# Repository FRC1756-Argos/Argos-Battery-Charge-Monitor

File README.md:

# Argos-Battery-Charge-Monitor
System to monitor a set of charging batteries

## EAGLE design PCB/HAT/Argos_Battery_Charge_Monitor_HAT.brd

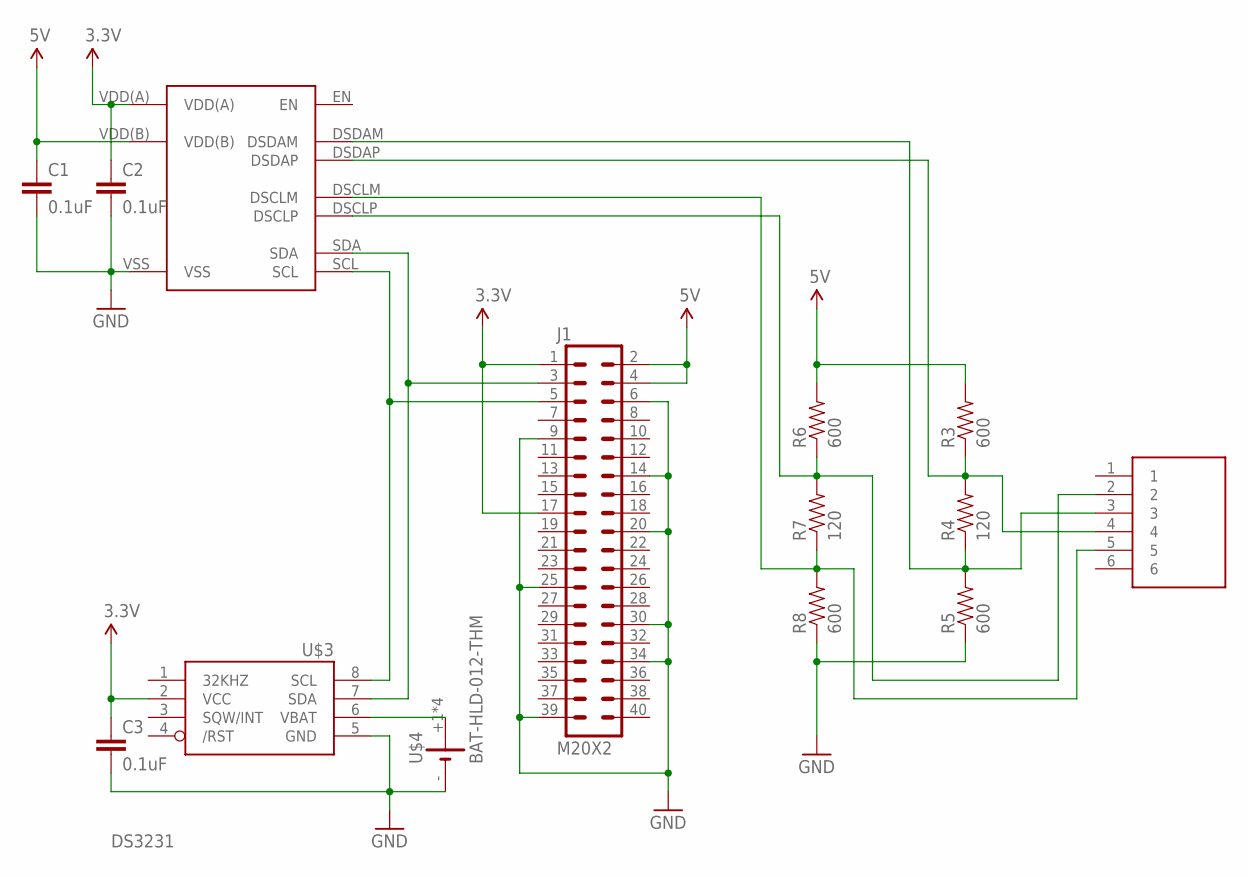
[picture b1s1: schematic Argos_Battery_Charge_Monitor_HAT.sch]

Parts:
C1, C2, C3: 0.1uF; 0805
J1: M20X2; 2X20
R3, R5, R6, R8: 600; 0805
R4, R7: 120; 0805
U$1: E5566-Q0LK22-L
U$2: SOP50P490X110-10N
U$3: DS3231MZ; SOIC8
U$4: BAT-HLD-012-THM

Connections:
3.3V: C2.1, C3.1, J1.1, J1.17, U$2.VDD(A), U$3.2 (VCC)
5V: C1.1, J1.2, J1.4, R3.2, R6.2, U$2.VDD(B)
D_SCL_M: R7.1, R8.2, U$1.5, U$2.DSCLM
D_SCL_P: R6.1, R7.2, U$1.2, U$2.DSCLP
D_SDA_M: R4.1, R5.2, U$1.3, U$2.DSDAM
D_SDA_P: R3.1, R4.2, U$1.4, U$2.DSDAP
GND: C1.2, C2.2, C3.2, J1.6, J1.9, J1.14, J1.20, J1.25, J1.30, J1.34, J1.39, R5.1, R8.1, U$2.VSS, U$3.5 (GND), U$4.-
unnamed: U$3.6 (VBAT), U$4.+1 (+), U$4.+2 (+), U$4.+3 (+), U$4.+4 (+)
SCL: J1.5, U$2.SCL, U$3.8 (SCL)
SDA: J1.3, U$2.SDA, U$3.7 (SDA)

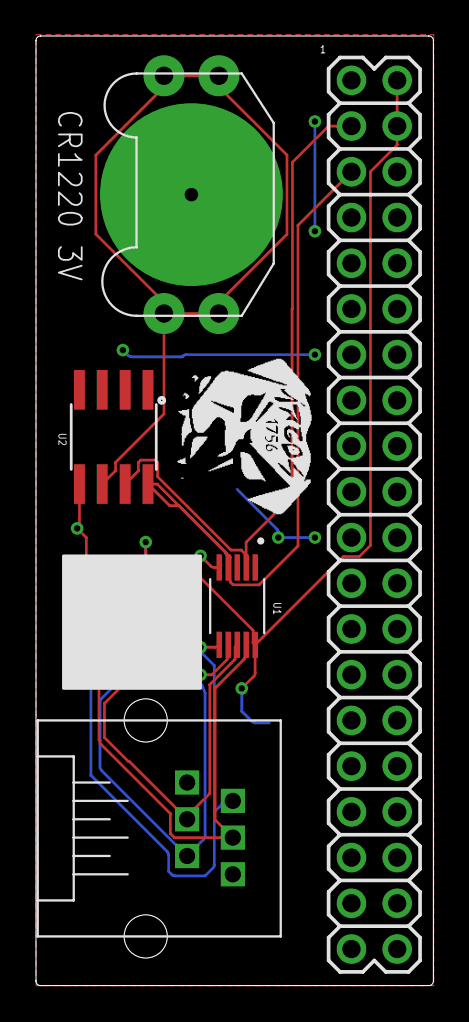
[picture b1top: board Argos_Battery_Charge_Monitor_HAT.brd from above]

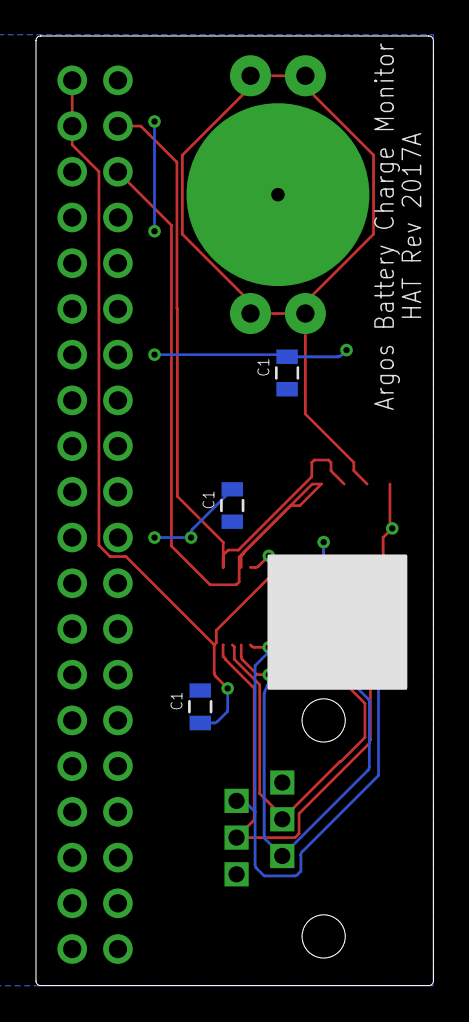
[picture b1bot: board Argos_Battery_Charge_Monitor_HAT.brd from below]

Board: 2 copper layers, 22.1 x 52.8 mm, 14 parts (6 on the bottom side), 10 nets.

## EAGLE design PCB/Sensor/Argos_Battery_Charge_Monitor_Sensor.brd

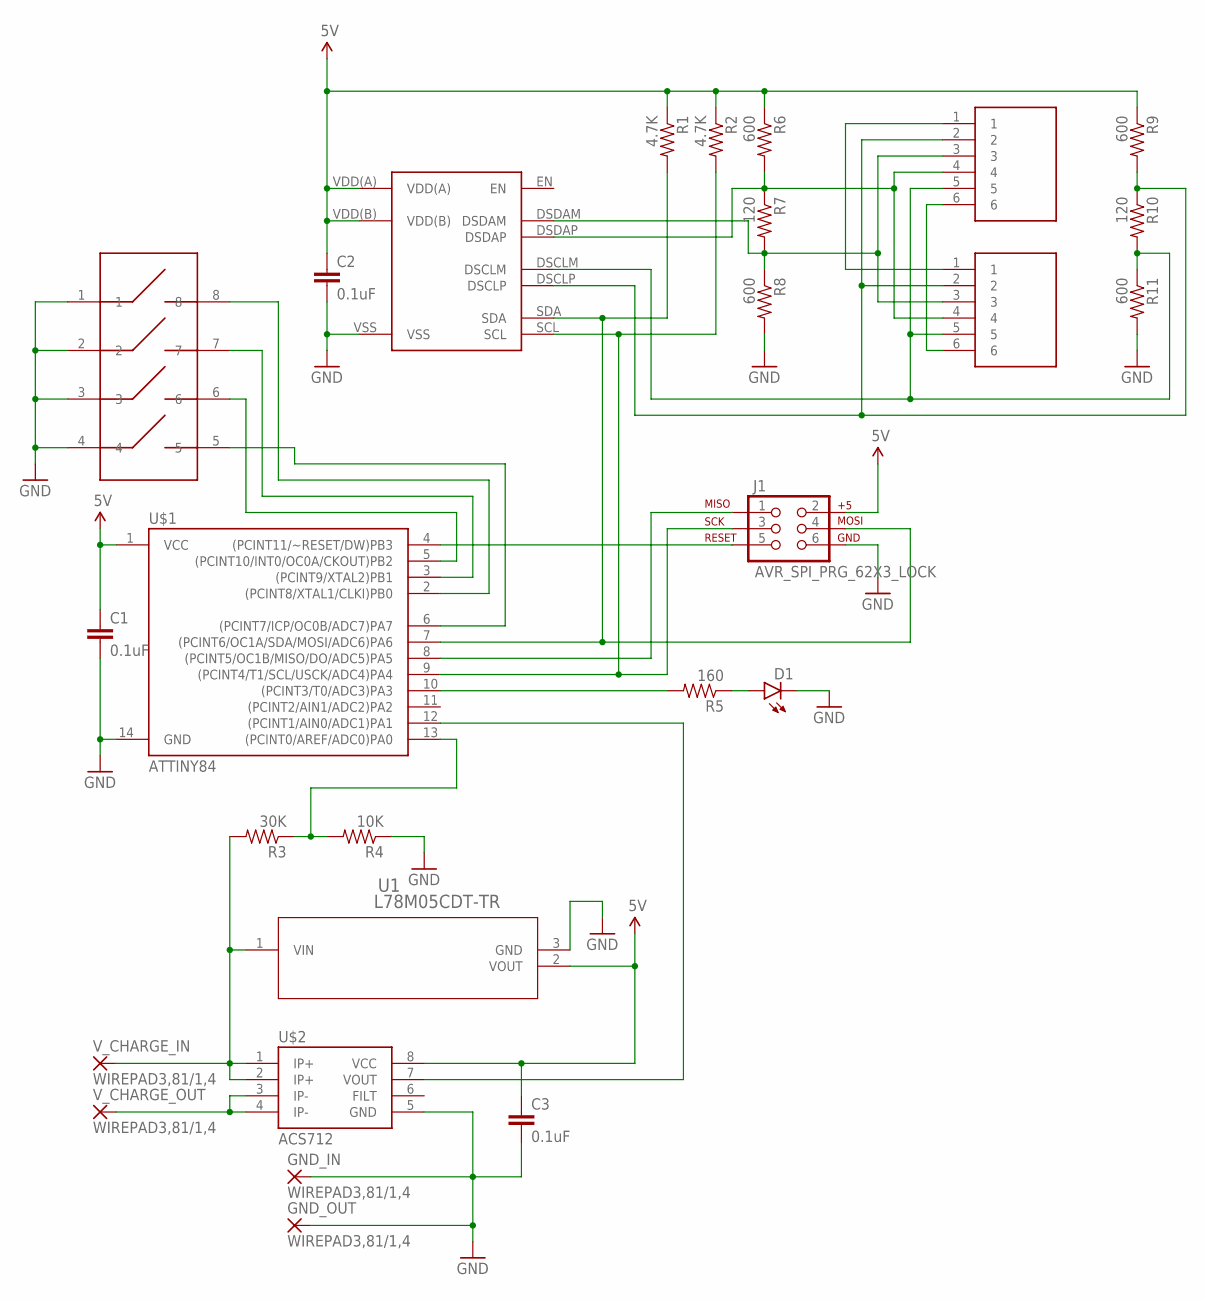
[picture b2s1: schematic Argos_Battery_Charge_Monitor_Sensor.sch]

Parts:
C1, C2, C3: 0.1uF; 0805
D1: LED3MM
GND_IN: WIREPAD3,81/1,4; 3,81/1,4
GND_OUT: WIREPAD3,81/1,4; 3,81/1,4
J1: AVR_SPI_PRG_62X3_LOCK; 2X3_LOCK
R1, R2: 4.7K; 0805
R3: 30K; 0805
R4: 10K; 0805
R5: 160; 0805
R6, R8, R9, R11: 600; 0805
R7, R10: 120; 0805
U1: L78M05CDT-TR; DPAK
U$1: ATTINY84; SO14
U$2: ACS712; SO08
U$3: SOP50P490X110-10N
U$4, U$5: E5566-Q0LK22-L
U$6: 210-4MS
V_CHARGE_IN: WIREPAD3,81/1,4; 3,81/1,4
V_CHARGE_OUT: WIREPAD3,81/1,4; 3,81/1,4

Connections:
5V: C1.1, C2.1, C3.1, J1.2, R1.1, R2.1, R6.1, R9.1, U1.2 (VOUT), U$1.1 (VCC), U$2.8 (VCC), U$3.VDD(A), U$3.VDD(B)
D_SCK_M: R10.2, R11.1, U$3.DSCLM, U$4.5, U$5.5
D_SCK_P: R9.2, R10.1, U$3.DSCLP, U$4.2, U$5.2
D_SDA_M: R7.2, R8.1, U$3.DSDAM, U$4.3, U$5.3
D_SDA_P: R6.2, R7.1, U$3.DSDAP, U$4.4, U$5.4
GND: C1.2, C2.2, C3.2, D1.K (C), GND_IN.1, GND_OUT.1, J1.6, R4.1, R8.2, R11.2, U1.3 (GND), U$1.14 (GND), U$2.5 (GND), U$3.VSS, U$6.1, U$6.2, U$6.3, U$6.4
unnamed: U$4.1, U$5.1
unnamed: U$1.5 ((PCINT10/INT0/OC0A/CKOUT)PB2), U$6.6
unnamed: U$1.3 ((PCINT9/XTAL2)PB1), U$6.7
unnamed: U$1.2 ((PCINT8/XTAL1/CLKI)PB0), U$6.8
unnamed: U$1.6 ((PCINT7/ICP/OC0B/ADC7)PA7), U$6.5
unnamed: U$4.6, U$5.6
unnamed: R3.2, U1.1 (VIN), U$2.1 (IP+), U$2.2 (IP+), V_CHARGE_IN.1
unnamed: R3.1, R4.2, U$1.13 ((PCINT0/AREF/ADC0)PA0)
unnamed: U$2.3 (IP-), U$2.4 (IP-), V_CHARGE_OUT.1
unnamed: U$1.12 ((PCINT1/AIN0/ADC1)PA1), U$2.7 (VOUT)
unnamed: D1.A, R5.1
unnamed: J1.5, U$1.4 ((PCINT11/~RESET/DW)PB3)
unnamed: J1.1, U$1.8 ((PCINT5/OC1B/MISO/DO/ADC5)PA5)
unnamed: R5.2, U$1.10 ((PCINT3/T0/ADC3)PA3)
SCL: J1.3, R2.2, U$1.9 ((PCINT4/T1/SCL/USCK/ADC4)PA4), U$3.SCL
SDA: J1.4, R1.2, U$1.7 ((PCINT6/OC1A/SDA/MOSI/ADC6)PA6), U$3.SDA

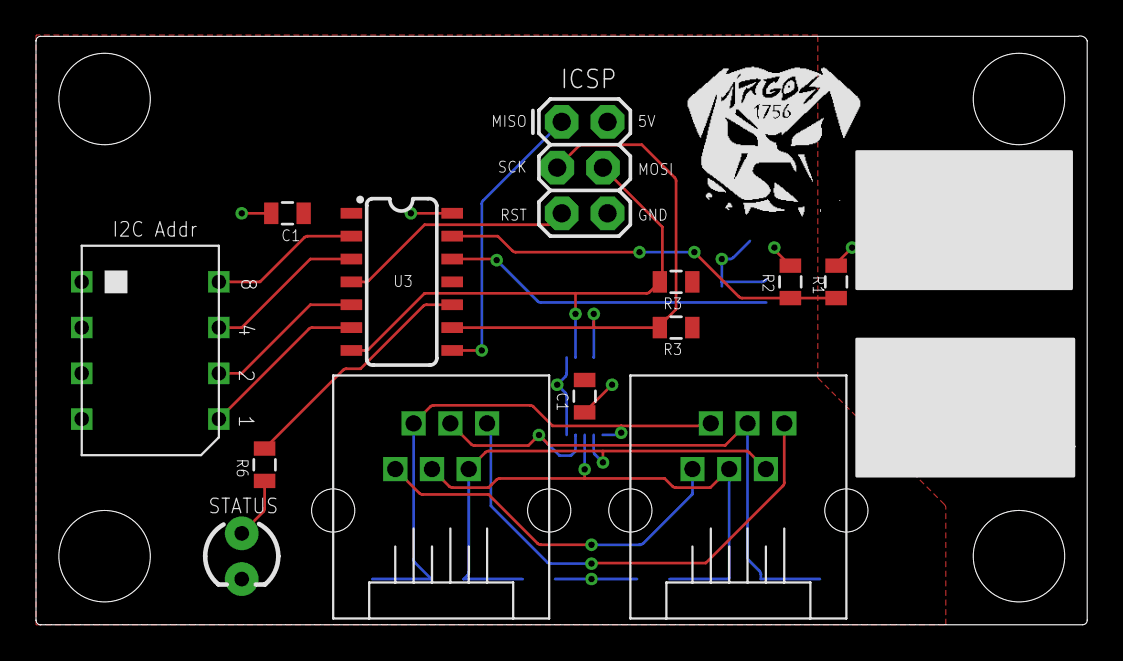
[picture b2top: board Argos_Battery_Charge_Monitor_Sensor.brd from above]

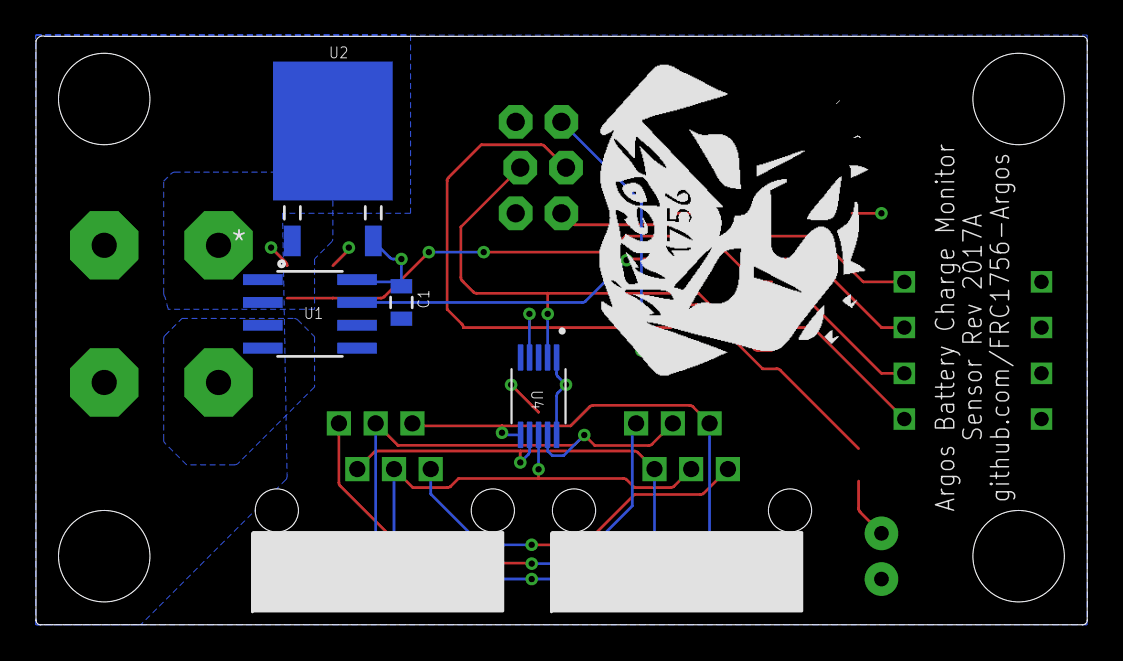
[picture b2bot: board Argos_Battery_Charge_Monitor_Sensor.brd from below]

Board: 2 copper layers, 58.4 x 32.7 mm, 27 parts (10 on the bottom side), 22 nets.

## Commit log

2017-11-18 Identified sensor components and finished sensor schematic
2017-11-20 2017 RevA boards complete
2017-11-20 Fixed quantity on a couple components
2017-12-12 Initial version with working I2C communications and voltage measurement. Current measurement seems good, too, but I haven't tested it thoroughly

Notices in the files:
parts and their libraries:
SparkFun-Capacitors: Licensing: Creative Commons ShareAlike 4.0 International - https://creativecommons.org/licenses/by-sa/4.0
